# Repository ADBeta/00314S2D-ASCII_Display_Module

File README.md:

# 00314S2D-ASCII 14 Segment 2 Digit LED Display Module    MkI

`00314S2D-ASCII` is a Daisychain-able 14 Segment, 2 Digit Display Module,
designed around the CH32V003 MCU.  
It receives `115200 Baud` UART Data, in standard ASCII Format, then displays
up to 2 Chars per Module. Any Additional chars will be transmitted down the 
chain of displays.

## How to Use
Connect a standard UART TX line, running at 115200 Baud to the
`RX` connection of the module, it is now ready to accept data.  
Any ASCII characters will be printed to the display, when one displays
buffer is full, it will echo the data on to the next display.  
Transmit `\n` or `\r` to clear the displays, this will propegate and 
clear all displays at once.  

To Daisychain the displays, connect `TX` from one, to `RX` of the next,
along with VCC and GND - this will allow you to connect [theoretically]
infinite displays in one chain, the only limit being current on VCC.

## Building a Module
BOM
```
RN1        330R 4*0603 Resistor Array
RN2        330R 4*0603 Resistor Array
RN3        330R 4*0603 Resistor Array
RN4        330R 4*0603 Resistor Array
R1         10R 0603
R2         2K2 0603
Q1         AO3400 N-Ch MOSFET SOT-23
Q2         AO3400 N-Ch MOSFET SOT-23
Q3         AO3400 N-Ch MOSFET SOT-23
C1         100nF 0603 MLCC
C2         1uF 0603 MLCC
U1         CH32V003FxPx TSSOP-20
DISP1      Red/Green/Blue 14 Segment 2 Digit Common Cathode Display
```

## Programming
Programming is done via the SWIO TestPoint on the back of the PCB.
Once programmed, SWIO is disabled to be used as a normal GPIO.
To Reprogram the deivce, connect a programmer to the SWIO pin, and
power cycle the device - this will put the device into program mode.

1) Connect SWIO Pin
2) Apply Power to the Module
3) Run `minichlink -D` to allow NRST to be a GPIO Pin
4) Flash the binary to the IC

NOTE: `make` will do both of these steps automatically if the user 
chooses to use that toolchain

> [TODO]
> Make MkII PCB with better programming ports  
> Make MkII PCB have MCU and resistors on rear side for easier repair (?)  
> Build automatic testing jig to validate modules before displays are attached  
> Investigate segment failure issue  

----
MIT License
Copyright (c) 2024 ADBeta

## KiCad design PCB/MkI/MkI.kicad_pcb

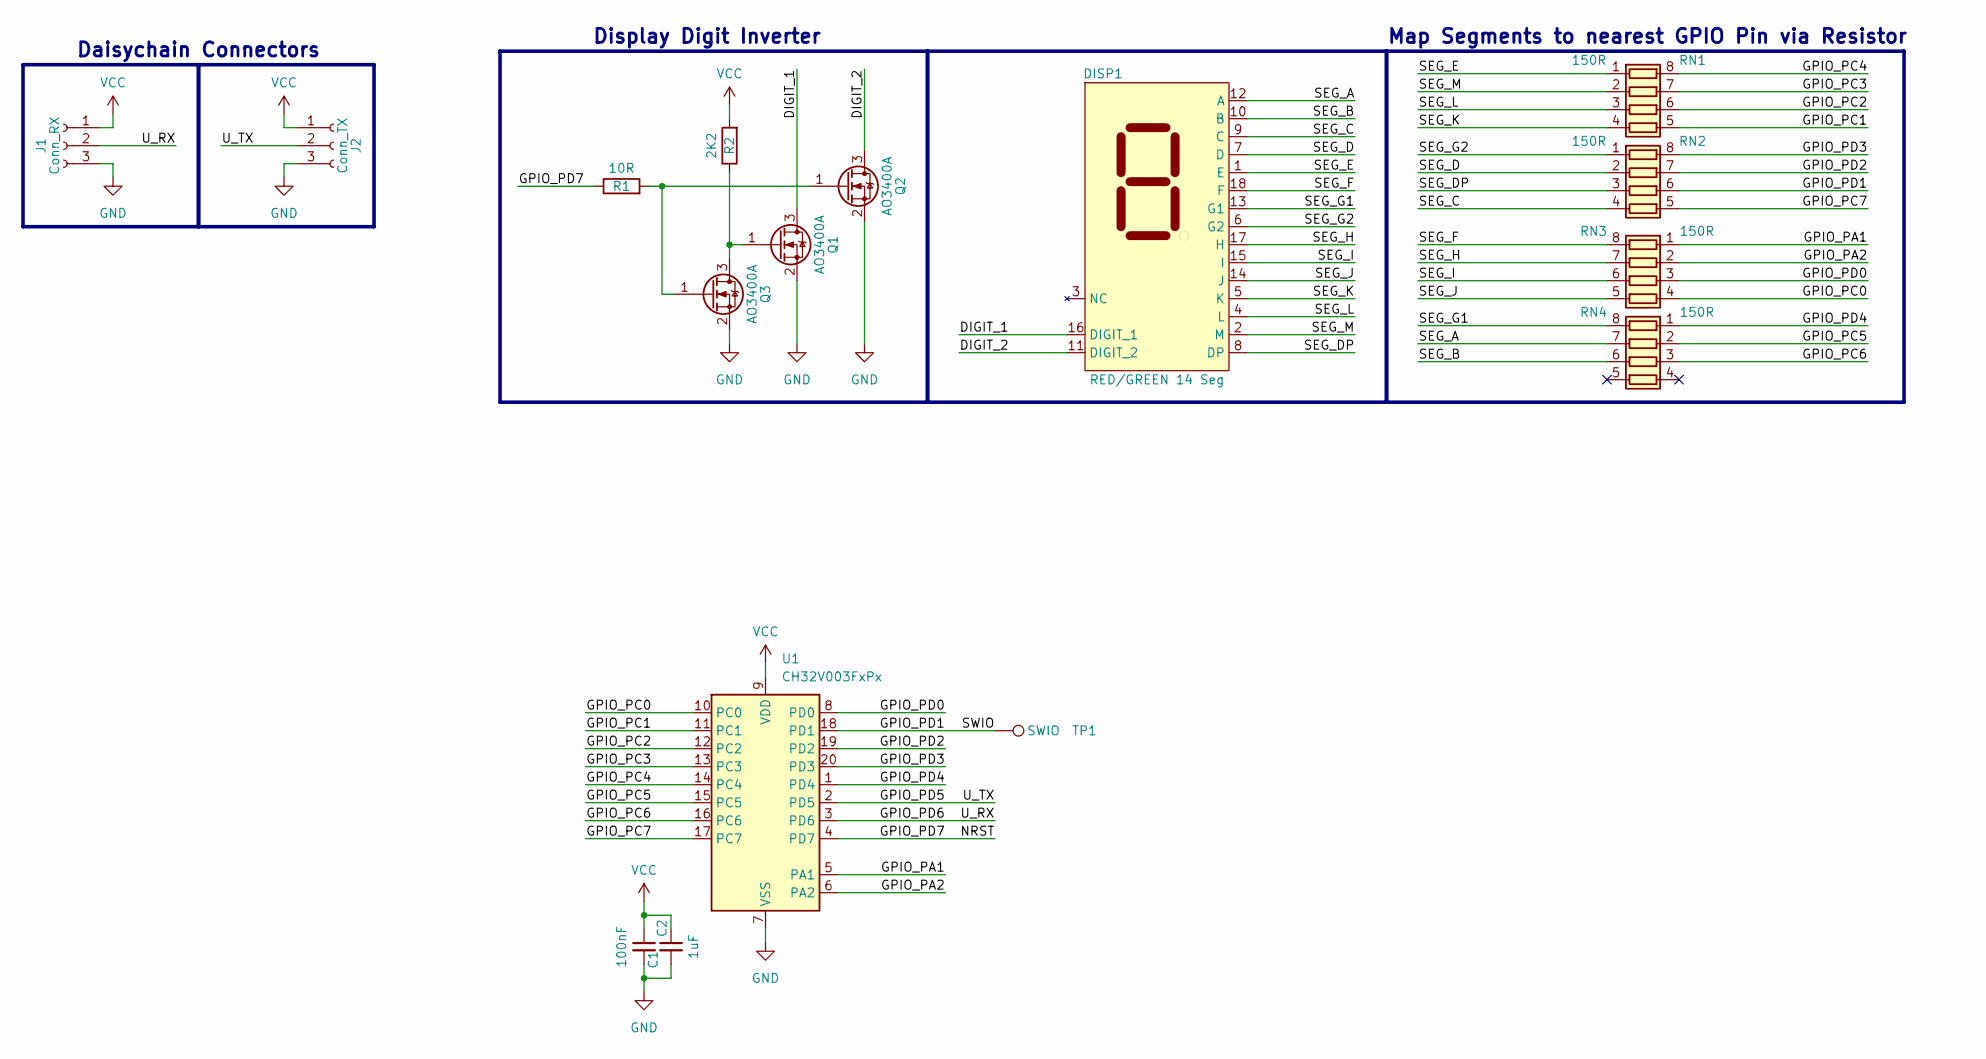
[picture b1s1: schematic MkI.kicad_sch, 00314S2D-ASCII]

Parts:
C1: 100nF; C_0603_1608Metric
C2: 1uF; C_0603_1608Metric
DISP1: RED/GREEN 14 Seg; 14_Seg_2_Digit_Display
J1: Conn_RX; Conn_Daisy_Chain
J2: Conn_TX; Conn_Daisy_Chain
Q1, Q2, Q3: AO3400A; SOT-23_Clean
R1: 10R; R_0603_1608Metric
R2: 2K2; R_0603_1608Metric
RN1, RN2, RN3, RN4: 150R; R_Array_Convex_4x0603
TP1: SWIO; TestPoint_Pad_D1.0mm
U1: CH32V003FxPx; TSSOP-20_4.4x6.5mm_P0.65mm

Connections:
/DIGIT_1: DISP1.16 (DIGIT_1), Q1.3 (D)
/DIGIT_2: DISP1.11 (DIGIT_2), Q2.3 (D)
/GPIO_PA1: RN3.1 (R1.1), U1.5 (PA1)
/GPIO_PA2: RN3.2 (R2.1), U1.6 (PA2)
/GPIO_PC0: RN3.4 (R4.1), U1.10 (PC0)
/GPIO_PC1: RN1.5 (R4.2), U1.11 (PC1)
/GPIO_PC2: RN1.6 (R3.2), U1.12 (PC2)
/GPIO_PC3: RN1.7 (R2.2), U1.13 (PC3)
/GPIO_PC4: RN1.8 (R1.2), U1.14 (PC4)
/GPIO_PC5: RN4.2 (R2.1), U1.15 (PC5)
/GPIO_PC6: RN4.3 (R3.1), U1.16 (PC6)
/GPIO_PC7: RN2.5 (R4.2), U1.17 (PC7)
/GPIO_PD0: RN3.3 (R3.1), U1.8 (PD0)
/GPIO_PD1: RN2.6 (R3.2), TP1.1, U1.18 (PD1)
/GPIO_PD2: RN2.7 (R2.2), U1.19 (PD2)
/GPIO_PD3: RN2.8 (R1.2), U1.20 (PD3)
/GPIO_PD4: RN4.1 (R1.1), U1.1 (PD4)
/GPIO_PD5: J2.2, U1.2 (PD5)
/GPIO_PD6: J1.2, U1.3 (PD6)
/GPIO_PD7: R1.1, U1.4 (PD7)
/SEG_A: DISP1.12 (A), RN4.7 (R2.2)
/SEG_B: DISP1.10 (B), RN4.6 (R3.2)
/SEG_C: DISP1.9 (C), RN2.4 (R4.1)
/SEG_D: DISP1.7 (D), RN2.2 (R2.1)
/SEG_DP: DISP1.8 (DP), RN2.3 (R3.1)
/SEG_E: DISP1.1 (E), RN1.1 (R1.1)
/SEG_F: DISP1.18 (F), RN3.8 (R1.2)
/SEG_G1: DISP1.13 (G1), RN4.8 (R1.2)
/SEG_G2: DISP1.6 (G2), RN2.1 (R1.1)
/SEG_H: DISP1.17 (H), RN3.7 (R2.2)
/SEG_I: DISP1.15 (I), RN3.6 (R3.2)
/SEG_J: DISP1.14 (J), RN3.5 (R4.2)
/SEG_K: DISP1.5 (K), RN1.4 (R4.1)
/SEG_L: DISP1.4 (L), RN1.3 (R3.1)
/SEG_M: DISP1.2 (M), RN1.2 (R2.1)
GND: C1.2, C2.2, J1.3, J2.3, Q1.2 (S), Q2.2 (S), Q3.2 (S), U1.7 (VSS)
unnamed: Q1.1 (G), Q3.3 (D), R2.1
unnamed: Q2.1 (G), Q3.1 (G), R1.2
VCC: C1.1, C2.1, J1.1, J2.1, R2.2, U1.9 (VDD)

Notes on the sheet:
Display Digit Inverter
Map Segments to nearest GPIO Pin via Resistor
Daisychain Connectors

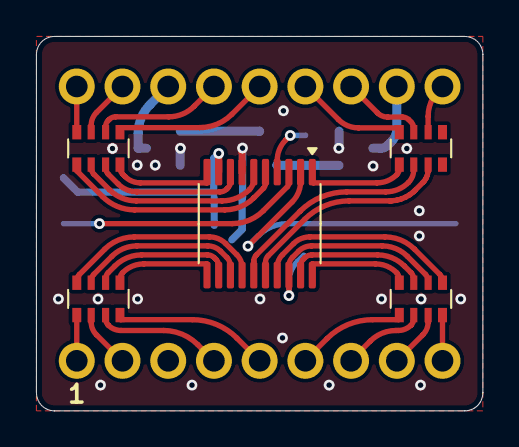
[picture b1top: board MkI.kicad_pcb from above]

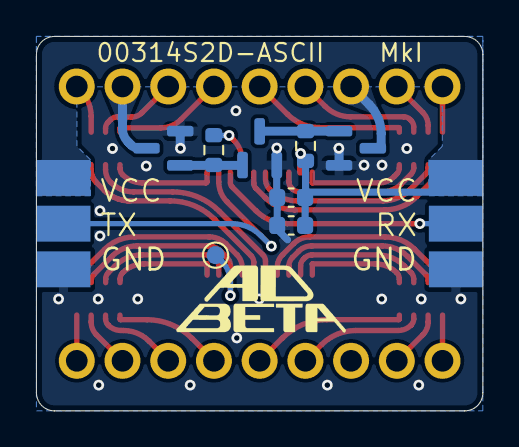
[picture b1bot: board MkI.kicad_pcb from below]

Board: 2 copper layers, 24.8 x 20.8 mm, 16 parts (10 on the bottom side), 39 nets.

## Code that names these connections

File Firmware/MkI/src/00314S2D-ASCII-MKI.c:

/******************************************************************************
* 00314S2D-ASCII MkI
* A 2 Digit, 14 Segment Display Module using the CH32V003 MCU.
* For more information see the GitHub: 
* https://github.com/ADBeta/00314S2D-ASCII_Display_Module
*
* Functional Description:
* Each board Receives data via RX, and transmits it via TX at 115200 Baud
* When receiving data, each unit refils its internal display buffer, when it 
* is full, any incoming data is echoed directly to TX down the chain - due to
* this you can have a theoretically infinte number of displays 
*
* When power is applied, a self check takes place to look for the presense of
* a WCHLink programmer - if SWIO is asserted HIGH, a programmer is present,
* and the deivce will boot into a blank waiting mode to be programmed.
* - if the SWIO pin is left open, it boots into regular display mode
*
* Ver 0.1    14 Oct 2024 
* ADBeta (c) 2024
******************************************************************************/
#include "ch32v003fun.h"
#include "lib_gpioctrl.h"
#include "lib_uart.h"

#include "font.h"

/*** Macros ******************************************************************/
#define SYSTICK_ONE_MILLISECOND ((uint32_t)FUNCONF_SYSTEM_CORE_CLOCK / 1000)
#define SYSTICK_ONE_MICROSECOND ((uint32_t)FUNCONF_SYSTEM_CORE_CLOCK / 1000000)
#define millis() (g_systick_millis)
#define micros() (SysTick->CNT / SYSTICK_ONE_MICROSECOND)

// Timing Variables
#define DISPLAY_REFRESH_MILLIS 2

/*** Globals *****************************************************************/
// Incremented in the SysTick IRQ once per millisecond
volatile uint32_t g_systick_millis;

// Display Data Array [0] = Left    [1] = Right
uint16_t g_seg_data[2];

// Digit Pin
static const GPIO_PIN digit_pin = GPIO_PD7;

// Segment Pins
static const GPIO_PIN segment_pin[15] = {
	GPIO_PC5,    // A
	GPIO_PC6,    // B
	GPIO_PC7,    // C
	GPIO_PD2,    // D
	GPIO_PC4,    // E
	GPIO_PA1,    // F
	GPIO_PD4,    // G1
	GPIO_PD3,    // G2
	GPIO_PA2,    // H
	GPIO_PD0,    // I
	GPIO_PC0,    // J
	GPIO_PC1,    // K
	GPIO_PC2,    // L
	GPIO_PC3,    // M
	GPIO_PD1,    // DP
};

/*** Forward Declaration *****************************************************/
/// @brief Initialise the SysTick interrupt to incriment every 1 millisecond
/// @param None
/// @return None
static void systick_init(void);

/// @brief SysTick IRQ
/// @param none
/// @return none
__attribute__((interrupt))
void SysTick_Handler(void);

static void detect_programmer(void);

/// @brief Sets all segments in the display
/// @param uint16_t segment bits
/// @return None
__attribute__((always_inline))
static inline void disp_write(const uint16_t seg_data);

/// @brief Initialises the Display pins and sets it into a blank state
/// @param None
/// @return None
static void disp_init(void);

/// @brief Update which segment is visible, and set the Segment pins
/// @param None
/// @return None
static void disp_refresh(void);

/*** Main ********************************************************************/
int main(void)
{
	SystemInit();
	systick_init();

	// Checks if the SWIO Porgramming pin is connected. Waits forever if so 
	detect_programmer();
	
	// Initialise the display. Disables SWIO
	disp_init();
	
	// Setup and Initialise UART (Default Pinout)
	uart_config_t uart_conf = {
		.baudrate    = UART_BAUD_115200,
		.wordlength  = UART_WORDLENGTH_8,
		.parity      = UART_PARITY_NONE,
		.stopbits    = UART_STOPBITS_ONE,
		.flowctrl    = UART_FLOWCTRL_NONE,
	};

	uart_init(&uart_conf);	

	// Display Refresh and UART Parsing loop
	while(1)
	{
		// Refresh the display when the target millis are reached
		static uint32_t disp_last_refresh = 0;
		if(millis() - disp_last_refresh > DISPLAY_REFRESH_MILLIS)
		{
			disp_refresh();
			disp_last_refresh = millis();
		}
		
		// An interrupt will handle all display setting. Only refresh in loop
	}
}


/*** Functions ***************************************************************/
static void systick_init(void)
{
	// Reset any pre-existing configuration
	SysTick->CTLR = 0x0000;
	
	// Set the compare register to trigger once per millisecond
	SysTick->CMP = SYSTICK_ONE_MILLISECOND - 1;

	// Reset the Count Register, and the global millis counter to 0
	SysTick->CNT = 0x00000000;
	g_systick_millis = 0x00000000;
	
	// Set the SysTick Configuration
	// NOTE: By not setting SYSTICK_CTLR_STRE, we maintain compatibility with
	// busywait delay funtions used by ch32v003_fun.
	SysTick->CTLR |= SYSTICK_CTLR_STE   |  // Enable Counter
	                 SYSTICK_CTLR_STIE  |  // Enable Interrupts
	                 SYSTICK_CTLR_STCLK ;  // Set Clock Source to HCLK/1
	
	// Enable the SysTick IRQ
	NVIC_EnableIRQ(SysTicK_IRQn);
}


__attribute__((interrupt))
void SysTick_Handler(void)
{
	// Increment the Compare Register for the next trigger
	SysTick->CMP += SYSTICK_ONE_MILLISECOND;

	// Clear the trigger state for the next IRQ
	SysTick->SR = 0x00000000;

	// Increment the milliseconds count
	g_systick_millis++;
}

static void detect_programmer(void)
{
	// Set PD1 (SWIO) to INPUT_PULLDOWN - the programmer pulls HIGH
	gpio_set_mode(GPIO_PD1, INPUT_PULLDOWN);
	// Wait for line to settle
	Delay_Ms(100);
	// Detect the SWIO pins' state
	if(gpio_digital_read(GPIO_PD1) == GPIO_HIGH)
	{
		// Stop pulling SWIO so programming can happen
		gpio_set_mode(GPIO_PD1, INPUT_FLOATING);
		// Wait
		while(1) { }
	}
}

__attribute__((always_inline))
static inline void disp_write(const uint16_t seg_data)
{
	for(uint16_t seg_idx = 0; seg_idx < 15; seg_idx++)
	{
		uint8_t seg_bit = (seg_data >> seg_idx) & 0x01;
		gpio_digital_write(segment_pin[seg_idx], seg_bit);
	}
}


static void disp_init(void)
{
	// Enable Alternate GPIO Funtionality and disable SWIO
	RCC->APB2PCENR |= RCC_APB2Periph_AFIO;
	AFIO->PCFR1    |= 0x04000000;

	// TODO: Using FLASH, set the option bit to dsiable the NRST Pin

	// Set all Segment GPIO to OUTPUT, LOW
	for(uint8_t seg_pin = 0; seg_pin < 15; seg_pin++)
	{
		gpio_set_mode(segment_pin[seg_pin], OUTPUT_10MHZ_PP);
		gpio_digital_write(segment_pin[seg_pin], GPIO_LOW);
	}

	// Set the Display Control Pin to OUTPUT, LOW
	gpio_set_mode(digit_pin, OUTPUT_10MHZ_PP);
	gpio_digital_write(digit_pin, GPIO_LOW);

	// Set the global display data to 0
	g_seg_data[0] = 0x0000;
	g_seg_data[1] = 0x0000;
}


static void disp_refresh(void)
{
	// Display Selection Pin state. 0 = Left    1 = Right 
	static uint8_t digit_state = 0;

	// Blank all the segments to prevent ghosting
	disp_write(0x0000);
	// Write the current digit state
	gpio_digital_write(digit_pin, digit_state);	
	// Write the global segment data to the segment chosen
	disp_write(g_seg_data[digit_state]);

	// Invert the digit_state for the next loop
	digit_state = !digit_state;
}


/*** IRQHandler for UART ****************************************************/
/// @brief UART Receiver Interrupt handler - Puts the data received into the
/// UART Ring Buffer
/// @param None
/// @return None
void USART1_IRQHandler(void) __attribute__((interrupt));
void USART1_IRQHandler(void)
{
	if(USART1->STATR & USART_STATR_RXNE) 
	{
		// Set 2 chars on this display, after that echo to the next display.
		static uint8_t char_idx = 0;
		bool echo_flag = 0;


		// Read from the DATAR Register to reset the flag
		uint8_t recv = (uint8_t)USART1->DATAR;

		/*** Handle incomming chars ******************************************/
		// Check if the received byte is a control char
		// Newline and CR are treated the same
		if(recv == ASCII_CONTROL_LINE_FEED || 
		   recv == ASCII_CONTROL_CARRIAGE_RETURN)
		{
			// Clear displays and reset char counter
			g_seg_data[0] = 0x0000;
			g_seg_data[1] = 0x0000;
			char_idx = 0;

			// Mark this byte to be echoed forward
			echo_flag = true;

		// NOTE: Add more control char beviour at this point
		
		// Any regular ASCII Char
		} else if(recv >= 0x20 && recv <= 0x7E)
		{
			if(char_idx < 2)
			{
				// Set the corresponding char with the received data
				g_seg_data[char_idx] = ascii_font[recv - 0x20];
				char_idx++;
			} else {
				// Set flag to re-transmit the received data
				echo_flag = true;
			}
		}


		// Transmit the received byte if the flag is set
		if(echo_flag)
		{
			while(!(USART1->STATR & USART_FLAG_TC));
			USART1->DATAR = recv;
		}
	}
}

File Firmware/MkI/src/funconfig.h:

#ifndef _FUNCONFIG_H
#define _FUNCONFIG_H

#define CH32V003                 1

// Enable/Disable overwriting of the RX Ring Buffer.
// Enabled:  Incomming data will overwrite older data in the buffer
// Disabled: Incomming data will not be added to the buffer until space is free
#define RX_RING_BUFFER_OVERWRITE

// NOTE: UART_ALTERNATE_1 will disable SWIO (PD1)
//  Pinout        TX        RX        CTS        RTS
//  Default       PD5       PD6       PD3        PC2
//  Alternate 1   PD0       PD1       PC3        PC2
//  Alternate 2   PD6       PD5       PC6        PC7
//  Alternate 3   PC0       PC1       PC6        PC7
#define UART_PINOUT_DEFAULT

#endif

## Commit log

2024-09-13 MkI PCB Finished
2024-09-13 Cleanup
2024-09-13 Started on font
2024-09-15 Added Images
2024-09-23 PCB Testing & Font complete
2024-09-26 SysTick based timing for display refresh
2024-10-12 Changed lib_uart to not use ring buffer
2024-10-13 Working Interrupt Handler
2024-10-13 Changed current limiting resistors
2024-10-13 Fixed 'a' character
2024-10-14 Added Programmer Detection
2024-10-14 Adjusted Programming Notes
2024-10-15 Tidy up
2024-10-15 Added beta version of demo script
2024-10-17 Added programming instructions
2024-10-29 Adjusted main program and makefile
